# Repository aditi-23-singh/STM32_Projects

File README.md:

## Distributed Dual-Node Stepper Motor Control System
Bi-Directional UART Communication | Dual STM32 | TMC2208 | Event-Driven Firmware

## Project Summary

Designed and implemented a distributed embedded control architecture using two STM32F051 microcontrollers communicating over bi-directional UART, where both nodes are capable of controlling the same stepper motor through a TMC2208 driver.

The system supports:

    Motor control from either board
    Real-time command arbitration
    Single click → Start/Stop
    Double click → Reverse direction
    Long press → Mode control
    Deterministic timer-based pulse generation
    LED-assisted hardware debugging

This project demonstrates distributed embedded design, peripheral-level control, communication protocol handling, and real-time event synchronization.

## System Architecture
Both STM32 boards:
    
    Scan user inputs
    Generate control commands
    Transmit and receive via UART
    Update motor state based on synchronized command logic

Motor control authority is dynamically managed through command synchronization.

## Core Engineering Components
1. Bi-Directional UART Communication
    
    Full-duplex UART configuration
    Interrupt-driven RX handling
    Lightweight command protocol
    Conflict handling logic
    Command acknowledgment strategy

Key focus areas:

    Clock accuracy & baud rate matching
    Framing reliability
    Data integrity verification
    Real-time synchronization

This demonstrates understanding of multi-node embedded systems and communication integrity.

2️. Event-Based Input Engine

Implemented a structured FSM to detect:

    Single click
    Double click (timing window based)
    Long press
    Double click triggers direction reversal.

Key techniques:
    
    Edge detection
    Non-blocking timing logic
    Debounce filtering
    Deterministic state transitions

This reflects correct event-driven firmware design rather than delay-based logic.

3️. Deterministic Motor Control (TMC2208 – STEP/DIR Mode)

    Hardware timer-based pulse generation
    Adjustable step frequency
    Direction toggling without step loss
    Safe enable/disable sequencing
    Synchronization with UART events

Ensured:
    
    No missed steps during direction changes
    No blocking delays
    Pulse width constraints respected
    Stable motor operation under distributed command input

4️. Distributed Control Handling
    
    Since both boards can issue motor commands:
    Implemented command synchronization logic
    Prevented inconsistent motor states
    Ensured deterministic behavior under concurrent inputs

This models real-world distributed embedded systems where multiple controllers share authority.

5️. Structured Hardware Debugging

Used LED signaling as a deterministic debug interface:

    UART transmit/receive confirmation
    State machine transitions
    Direction change verification
    Error detection states

Also performed:

    Register-level inspection
    Timer debugging
    Peripheral clock validation
    Step signal probing

Demonstrates disciplined debugging methodology.

## Engineering Challenges Solved

    Reliable double-click detection under timing constraints
    UART synchronization between two MCUs
    Preventing step loss during direction reversal
    Avoiding race conditions in distributed control
    Maintaining deterministic pulse generation

## What This Project Demonstrates

This project reflects:

    Multi-controller embedded system design
    Real-time event-driven firmware
    Deterministic motor control
    Communication protocol implementation
    Structured debugging methodology
    Hardware-level reasoning under timing constraints
    It models a scaled-down version of distributed hardware control systems used in industrial and silicon enablement environments.
    Maintaining deterministic pulse generation

## Potential Extensions
    
    DMA-based UART communication
    Acceleration ramp (trapezoidal velocity profile)
    Arbitration protocol with priority logic
    RTOS-based task scheduling
    Closed-loop feedback with encoder
    CRC-based command validation

### Author

Aditi Singh
B.Tech – Electronics & Communication Engineering
NIT Sikkim

Focus Areas:

    Embedded Systems
    VLSI & Chip Design
    Hardware-Software Co-Design
    System Architecture

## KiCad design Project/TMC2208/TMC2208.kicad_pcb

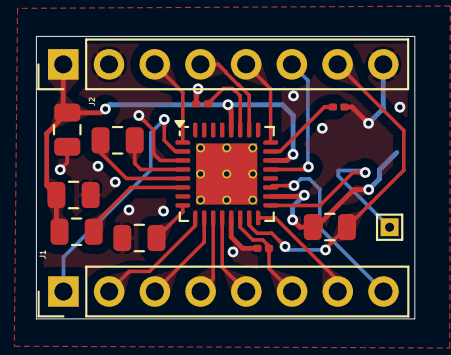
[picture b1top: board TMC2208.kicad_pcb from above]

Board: 2 copper layers, 21.0 x 15.7 mm, 14 parts (1 on the bottom side), 22 nets.

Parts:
C1, C3, C6: 100nF; C_0805_2012Metric
C2: 22nF; C_0805_2012Metric
C4: 130uF; C_0805_2012Metric
C5: 4.7uF; C_0805_2012Metric
J1, J2: Conn_01x08_Pin; PinHeader_1x08_P2.54mm_Vertical
R1, R2: 0.11E; R_0201_0603Metric
R5: 10K; R_0201_0603Metric
R6: R_Variable; Potentiometer_Bourns_TC33X_Vertical
U2: TMC2208-LA; TQFN-32-1EP_5x5mm_P0.5mm_EP3.4x3.4mm_ThermalVias
Vref1: TestPoint_THTPad_1.0x1.0mm_Drill0.5mm

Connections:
/DIAG: J1.4, U2.11 (DIAG)
/DIR: J1.8, U2.19 (DIR)
/EN: J1.1, U2.2 (ENN)
/INDEX: J1.5, U2.12 (INDEX)
/M1A: J2.5, U2.24 (OA1)
/M1B: J2.4, U2.26 (OB1)
/M2A: J2.6, U2.21 (OA2)
/M2B: J2.3, U2.1 (OB2)
/MS1: J1.2, U2.9 (MS1)
/MS2: J1.3, U2.10 (MS2)
/PDN_UART: J1.6, R5.2, U2.14 (PDN_UART)
/STEP: J1.7, U2.16 (STEP)
/VIO: C3.2, J2.7, U2.15 (VCC_IO)
/VM: C1.1, C4.1, C6.1, J2.1, U2.22 (VS), U2.28 (VS)
GND: C3.1, C4.2, C5.2, C6.2, J2.2, J2.8, R1.2, R2.2, R5.1, R6.1, U2.3 (GND), U2.13 (CLK), U2.18 (GND)
unnamed: C5.1, U2.8 (5VOUT)
unnamed: R2.1, U2.23 (BRA)
unnamed: R1.1, U2.27 (BRB)
unnamed: C2.1, U2.5 (CPI)
unnamed: C2.2, U2.4 (CPO)
unnamed: C1.2, U2.6 (VCP)
unnamed: R6.2, U2.17 (VREF), Vref1.1

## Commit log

2025-12-22 Initial commit: STM32F0 LED delay control with single/double click
2025-12-22 Initial commit: STM32_Projects
2025-12-22 Add hold1 project
2025-12-22 Add click1 as normal folder (remove nested git repo)
2025-12-22 Updated click1 and hold1 logic
2025-12-23 Half the delay when long press
2025-12-23 Chnages in hold1
2025-12-23 UpdateD Hold threshold
2025-12-23 Rename click folder to Projects
2025-12-23 Updated Readme documentation
2025-12-23 minor changes in readme
2025-12-24 Hold1 code changed for external LCD display
2025-12-24 Changes made in hold1 regarding over-writing
2025-12-24 Revert "Changes made in hold1 regarding over-writing"
    This reverts commit c38fc64fdb5875b58a89748a36d90eb9b5eff059.
2025-12-24 Major Refactor - Work In Progress
2025-12-24 Changes made in continuation of refactoring
2025-12-25 more refactored
2025-12-25 Ignore Drivers ,Debug directories and metdata
2025-12-25 minor chnages
2025-12-26 UART PEER TO PEER COMMUNICATION- WIP
2025-12-26 Further work on UART
2025-12-27 CORRECTED LAG BETWEEN TX AND RX
2025-12-27 CHANGED FUNCTIONALITY OF THREE MODES
2025-12-29 RESET THE TIMER BETWEEN EVENT
2025-12-29 Standard Variable Cases
2025-12-29 Refactored LEDApplications
2025-12-29 REFACTORED ButtonHandler- WIP
2025-12-29 ButtonHandler refactored-final
2025-12-29 FIXED BUG
2025-12-30 Refactored LCDApplications and UART
2025-12-30 Parameterized LED blink timings
2025-12-30 Refactored LCDApplication.c/.h into LCD_Driver.c/.h
2025-12-31 Implement 4-line LCD layout for local/remote mode and LED status
2025-12-31 removed comments
2025-12-31 FIXED DELAY BETWEEN CALLS
2025-12-31 Fixed Lag
2026-01-01 Removed Typecasting and Redundancy
2026-01-02 TMC2208 UART WITH STM32F0 -WIP
2026-01-05 TMC2208 WIP-2
2026-01-05 Full Duplex UART TMC2208
2026-01-05 CLEAN CODE
2026-01-06 set up IHOLD_IRUN, GCONF and IOIN
2026-01-06 Fixed Bugs
2026-01-08 Few Changes
2026-01-09 FIXED RxBuffer
2026-01-09 REFACTORED
2026-01-17 KiCAD-TMC2208
2026-01-23 Ki-CAD: TMC2208-WIP2
2026-01-24 Integrated 5X4 Matrix Keypad
2026-01-24 some fixes
2026-01-25 Integrated Motor Driver TMC2208 in Standalone Mode
